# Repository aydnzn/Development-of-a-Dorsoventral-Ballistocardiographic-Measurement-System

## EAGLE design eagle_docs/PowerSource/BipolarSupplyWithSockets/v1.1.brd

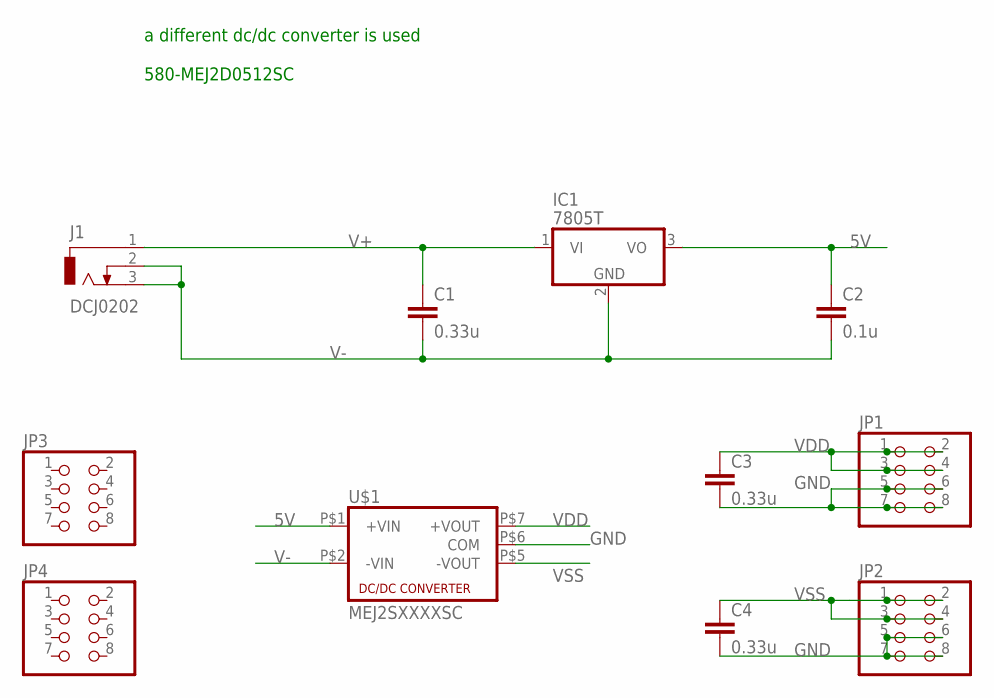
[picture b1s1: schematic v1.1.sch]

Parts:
C1, C3, C4: 0.33u; C050-045X075
C2: 0.1u; C050-045X075
IC1: 7805T; TO220H
J1: DCJ0202
JP1, JP2, JP3, JP4: PINHD-2X4; 2X04
U$1: MEJ2SXXXXSC; NMA

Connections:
5V: C2.1, IC1.3 (VO), U$1.P$1 (+VIN)
GND: C3.2, C4.2, JP1.5, JP1.6, JP1.7, JP1.8, JP2.5, JP2.6, JP2.7, JP2.8, U$1.P$6 (COM)
V+: C1.1, IC1.1 (VI), J1.1
V-: C1.2, C2.2, IC1.2 (GND), J1.2, J1.3, U$1.P$2 (-VIN)
VDD: C3.1, JP1.1, JP1.2, JP1.3, JP1.4, U$1.P$7 (+VOUT)
VSS: C4.1, JP2.1, JP2.2, JP2.3, JP2.4, U$1.P$5 (-VOUT)

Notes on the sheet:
a different dc/dc converter is used 580-MEJ2D0512SC

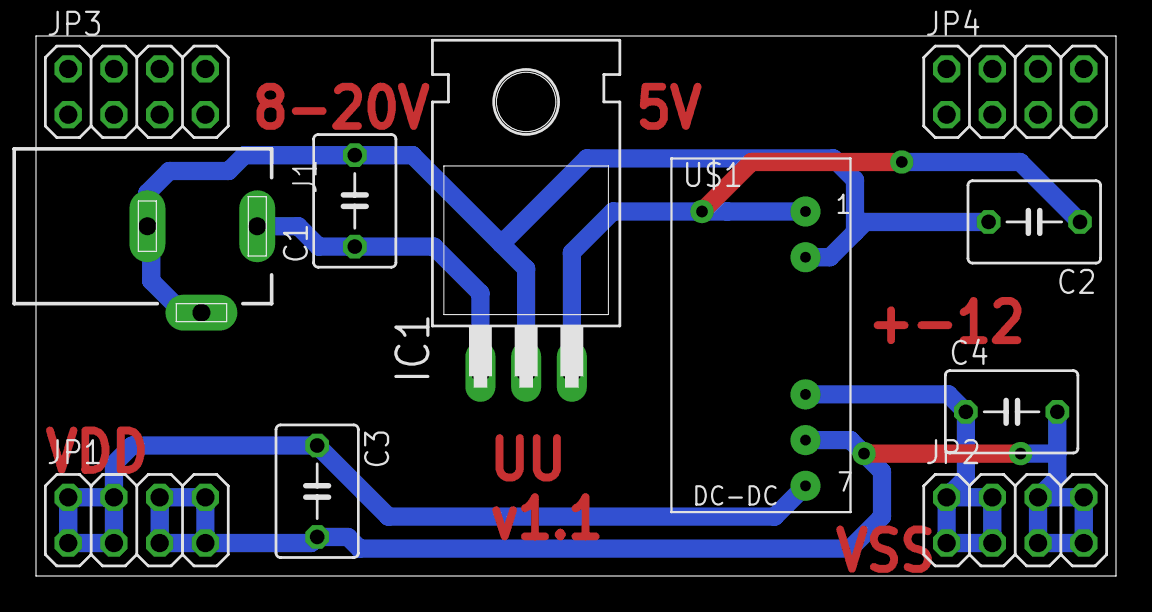
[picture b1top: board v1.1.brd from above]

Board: 2 copper layers, 60.0 x 30.0 mm, 11 parts (0 on the bottom side), 6 nets.

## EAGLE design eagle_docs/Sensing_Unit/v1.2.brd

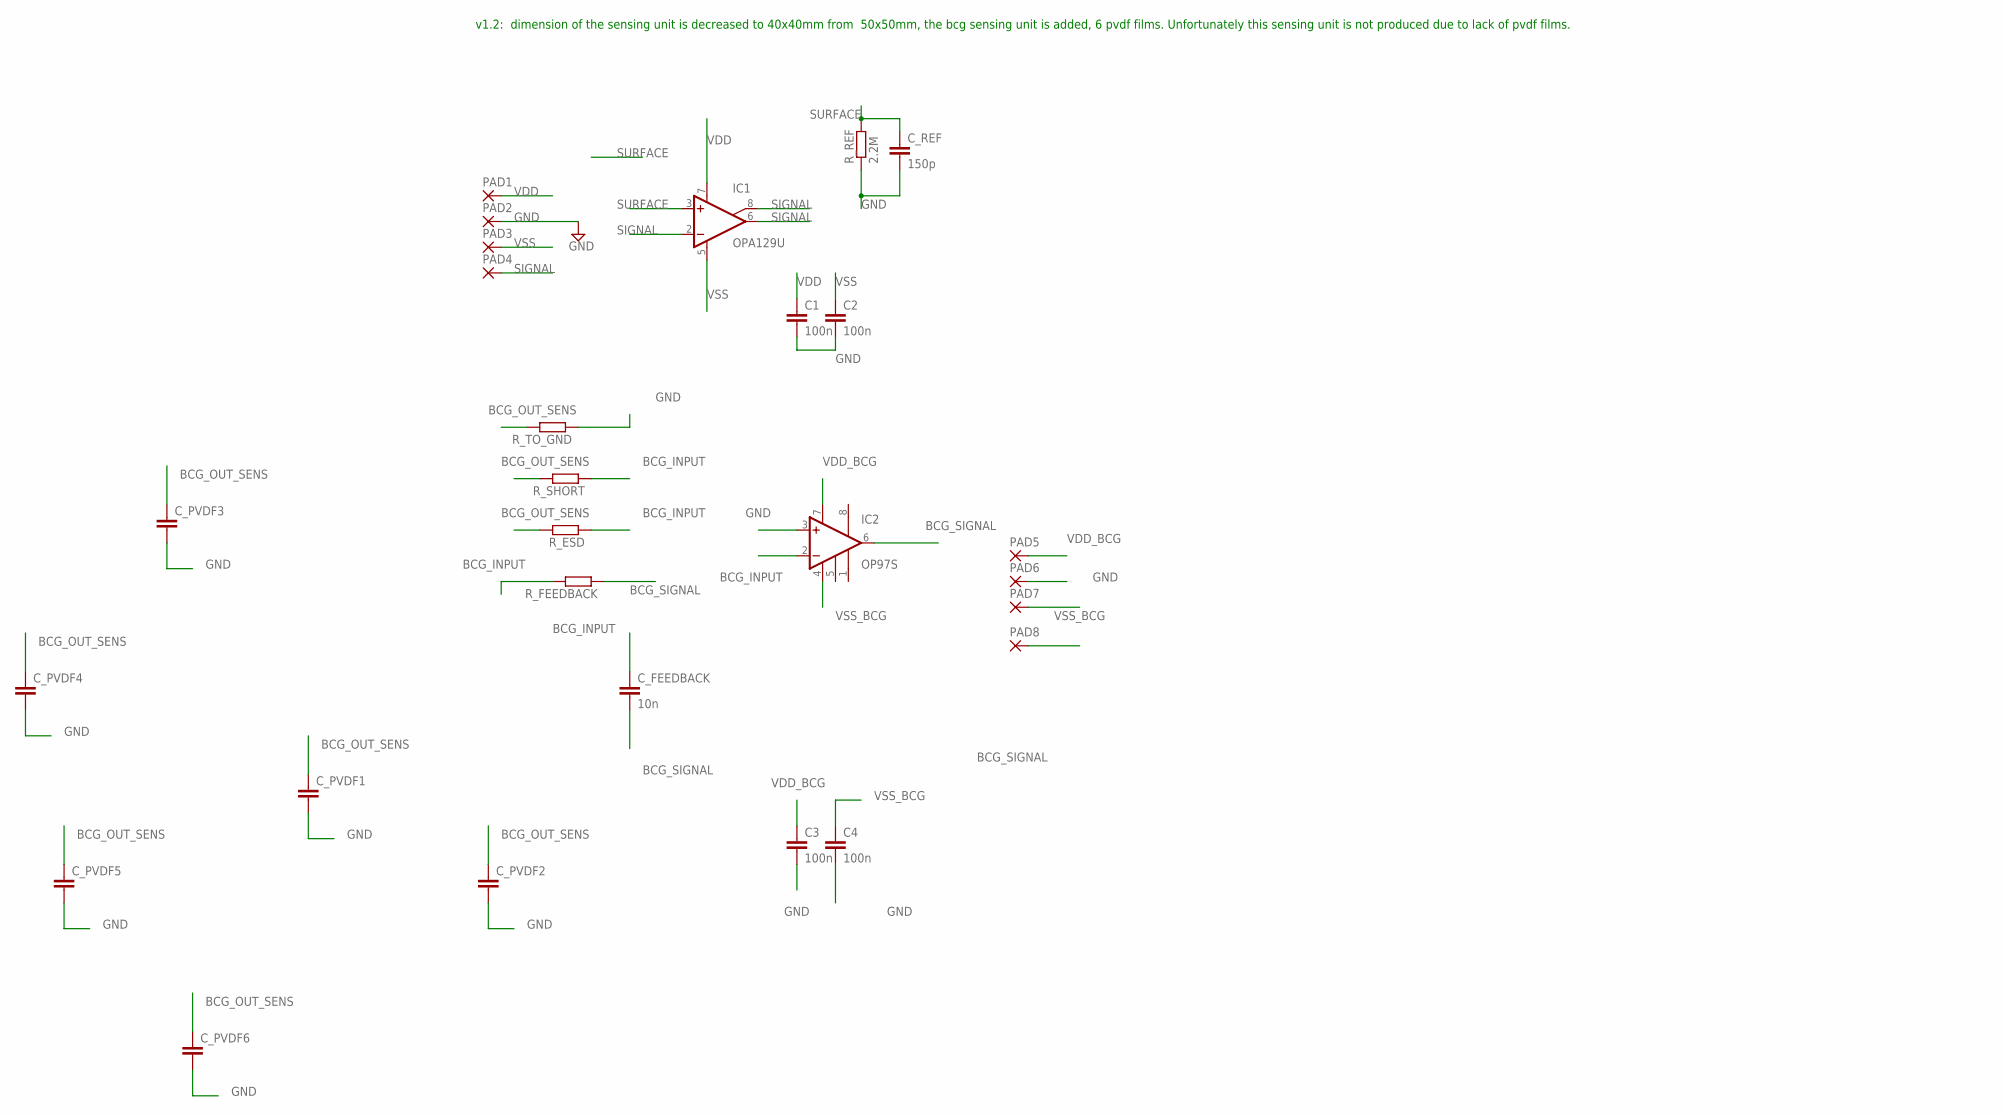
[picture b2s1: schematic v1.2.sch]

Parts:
C1, C2, C3, C4: 100n; C0805
C_FEEDBACK: 10n; C0805
C_PVDF1, C_PVDF2, C_PVDF3, C_PVDF4, C_PVDF5, C_PVDF6: C-EUC0805; C0805
C_REF: 150p; C0805
IC1: OPA129U; SO08
IC2: OP97S; SO08
PAD1, PAD2, PAD3, PAD4, PAD5, PAD6, PAD7, PAD8: SMD5; SMD2,54-5,08
R_ESD: 1M; M0805
R_FEEDBACK: 100M; M0805
R_REF: 2.2M; M0805
R_SHORT: 1M; M0805
R_TO_GND: 1M; M0805

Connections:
BCG_INPUT: C_FEEDBACK.1, IC2.2 (-IN), R_ESD.1, R_FEEDBACK.2, R_SHORT.1
BCG_OUT_SENS: C_PVDF1.1, C_PVDF2.1, C_PVDF3.1, C_PVDF4.1, C_PVDF5.1, C_PVDF6.1, R_ESD.2, R_SHORT.2, R_TO_GND.2
BCG_SIGNAL: C_FEEDBACK.2, IC2.6 (OUT), PAD8.1, R_FEEDBACK.1
GND: C1.2, C2.2, C3.2, C4.2, C_PVDF1.2, C_PVDF2.2, C_PVDF3.2, C_PVDF4.2, C_PVDF5.2, C_PVDF6.2, C_REF.2, IC2.3 (+IN), PAD2.1, PAD6.1, R_REF.1, R_TO_GND.1
SIGNAL: IC1.2 (-IN), IC1.6 (OUT), IC1.8 (SUBS), PAD4.1
SURFACE: C_REF.1, IC1.3 (+IN), R_REF.2
VDD: C1.1, IC1.7 (V+), PAD1.1
VDD_BCG: C3.1, IC2.7 (V+), PAD5.1
VSS: C2.1, IC1.5 (V-), PAD3.1
VSS_BCG: C4.1, IC2.4 (V-), PAD7.1

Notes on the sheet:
v1.2: dimension of the sensing unit is decreased to 40x40mm from 50x50mm, the bcg sensing unit is added, 6 pvdf films. Unfortunately this sensing unit is not produced due to lack of pvdf films.

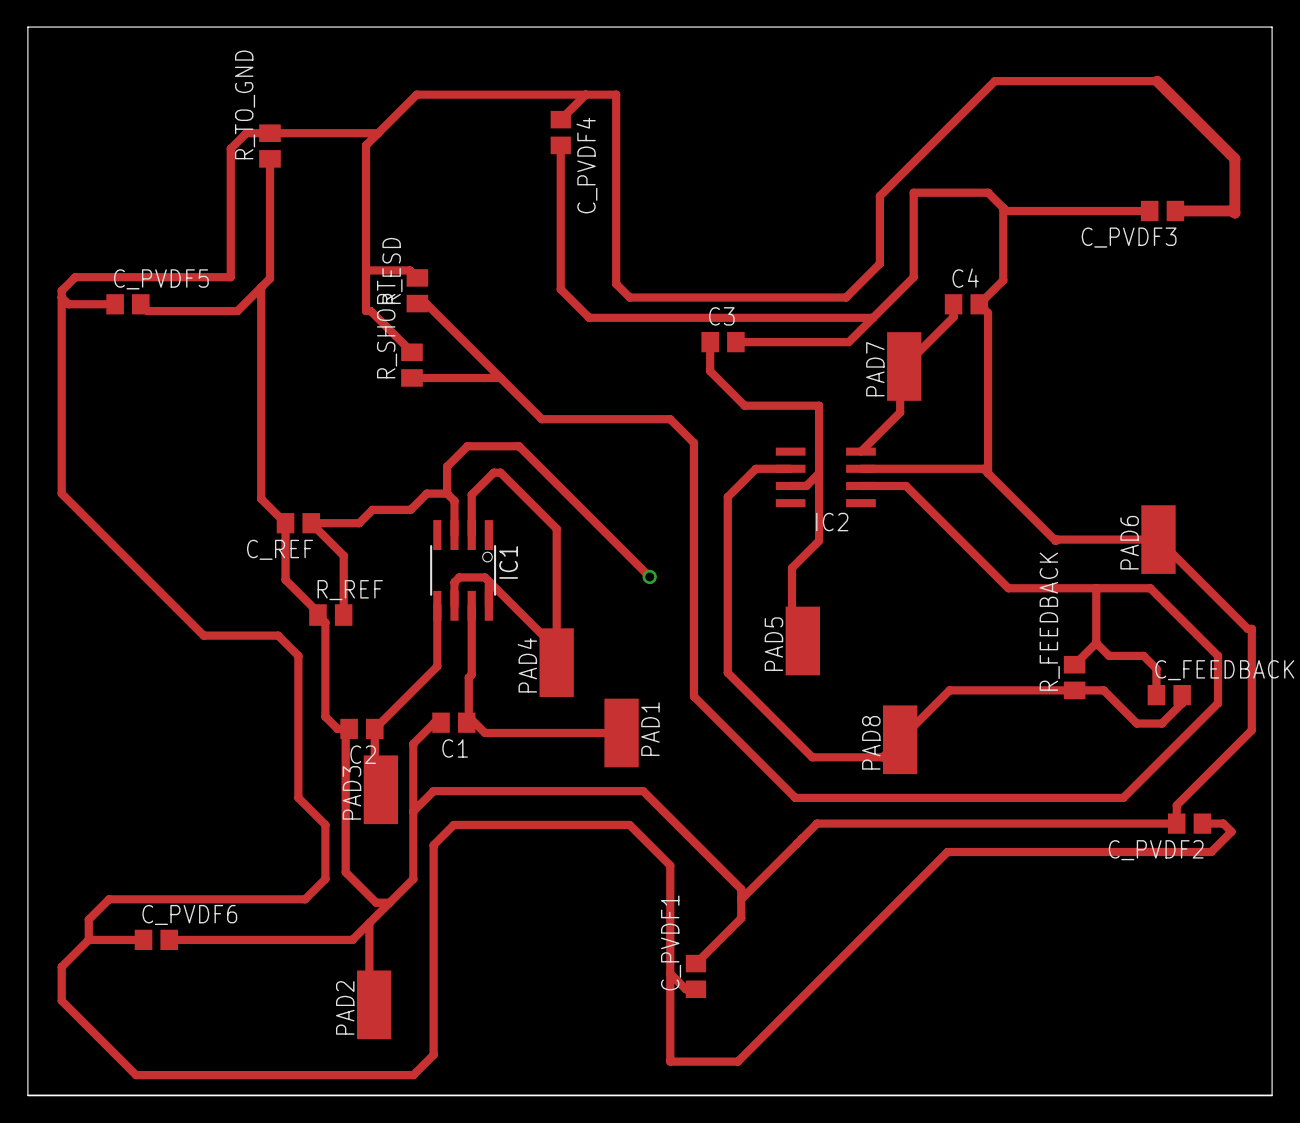
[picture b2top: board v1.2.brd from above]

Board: 2 copper layers, 92.0 x 79.0 mm, 27 parts (0 on the bottom side), 10 nets.

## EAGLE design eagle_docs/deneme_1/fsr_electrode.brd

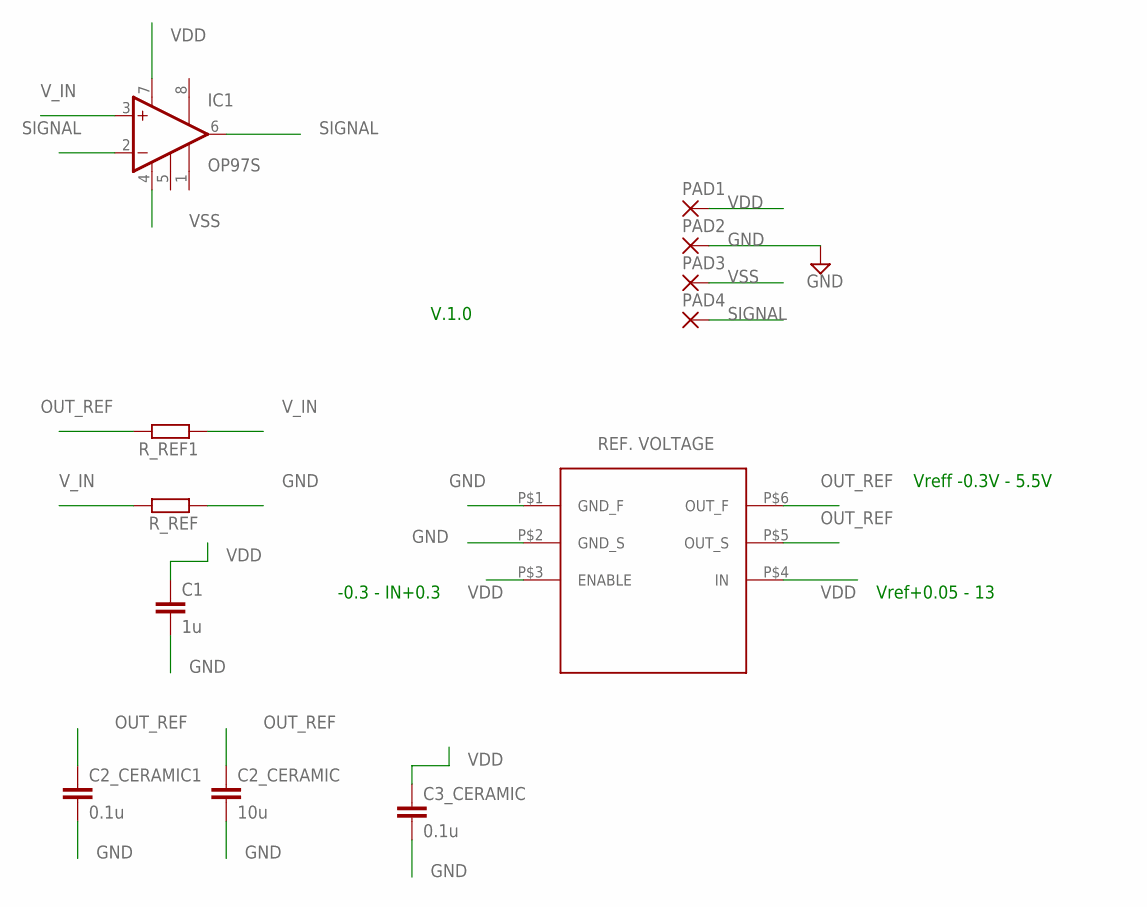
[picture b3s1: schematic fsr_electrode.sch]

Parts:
C1: 1u; C0805
C2_CERAMIC: 10u; C0805
C2_CERAMIC1, C3_CERAMIC: 0.1u; C0805
IC1: OP97S; SO08
PAD1, PAD2, PAD3, PAD4: SMD5; SMD2,54-5,08
REF3450: REF3450IDBVR; UZUN
R_REF, R_REF1: 10k; M0805

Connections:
GND: C1.2, C2_CERAMIC.2, C2_CERAMIC1.2, C3_CERAMIC.2, PAD2.1, REF3450.P$1 (GND_F), REF3450.P$2 (GND_S), R_REF.1
OUT_REF: C2_CERAMIC.1, C2_CERAMIC1.1, REF3450.P$5 (OUT_S), REF3450.P$6 (OUT_F), R_REF1.2
SIGNAL: IC1.2 (-IN), IC1.6 (OUT), PAD4.1
VDD: C1.1, C3_CERAMIC.1, IC1.7 (V+), PAD1.1, REF3450.P$3 (ENABLE), REF3450.P$4 (IN)
VSS: IC1.4 (V-), PAD3.1
V_IN: IC1.3 (+IN), R_REF.2, R_REF1.1

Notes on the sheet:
V.1.0
Vref+0.05 - 13
-0.3 - IN+0.3
Vreff -0.3V - 5.5V

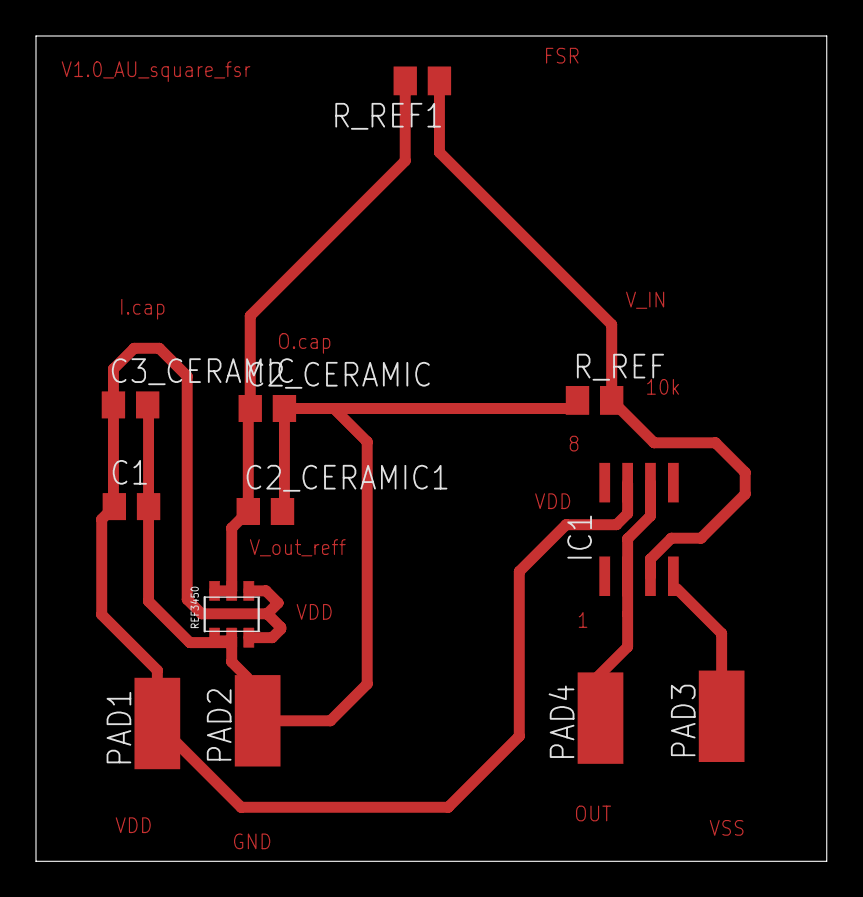
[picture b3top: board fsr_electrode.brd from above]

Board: 2 copper layers, 43.9 x 45.9 mm, 12 parts (0 on the bottom side), 6 nets.

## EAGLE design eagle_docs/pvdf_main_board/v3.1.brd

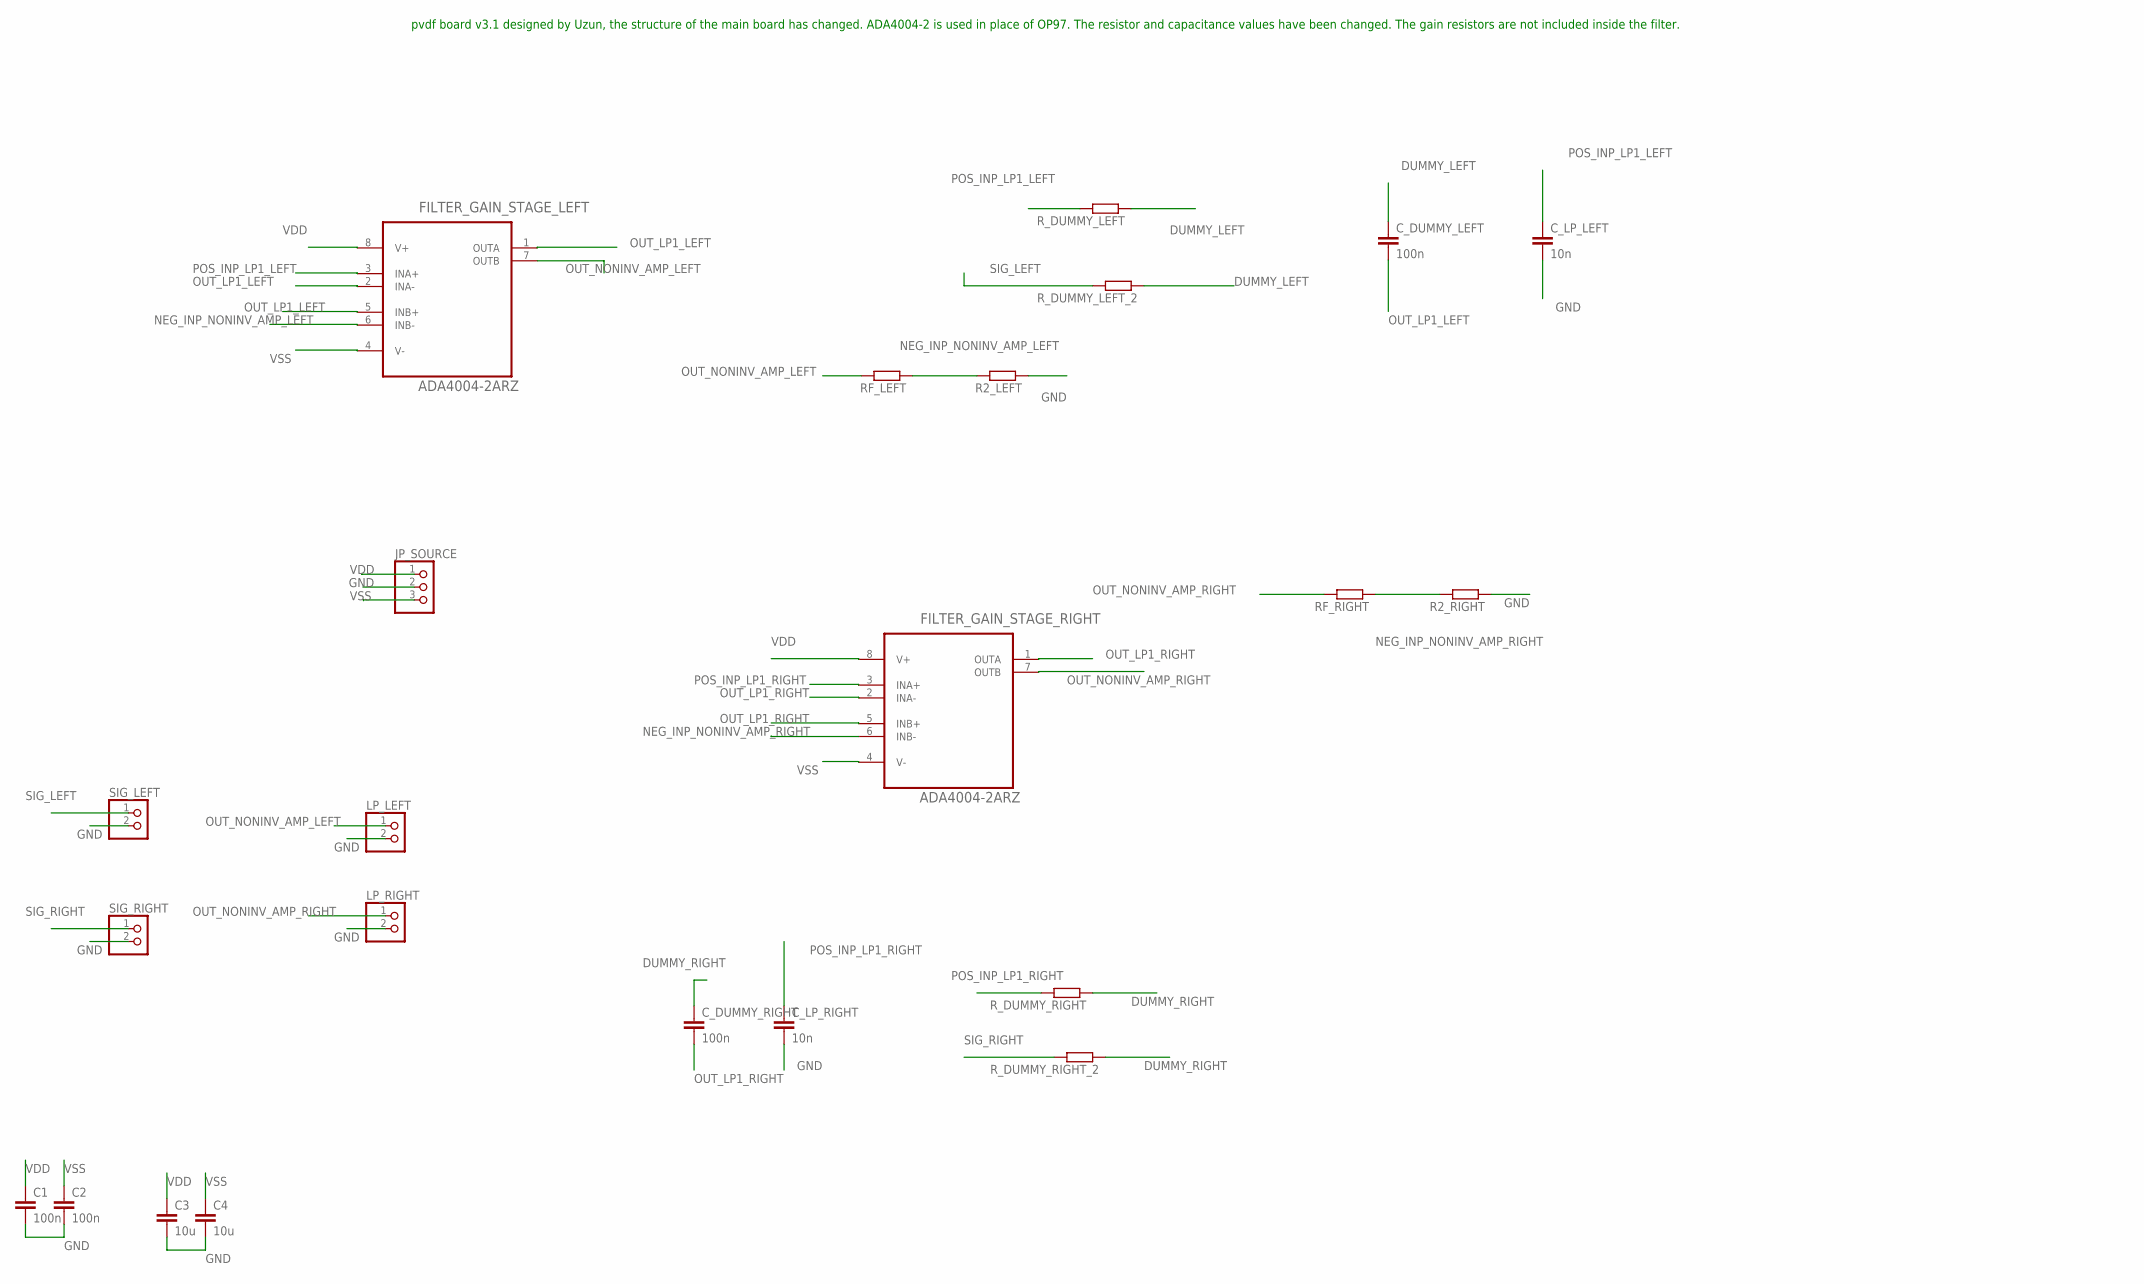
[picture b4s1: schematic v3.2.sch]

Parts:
C1, C2: 100n; C0805
C3, C4: 10u; C0805
C_DUMMY_LEFT: 100n; C0805
C_DUMMY_RIGHT: 100n; C0805
C_LP_LEFT: 10n; C0805
C_LP_RIGHT: 10n; C0805
FILTER_GAIN_STAGE_LEFT: ADA4004-2ARZ; SOIC127P600X175-8N
FILTER_GAIN_STAGE_RIGHT: ADA4004-2ARZ; SOIC127P600X175-8N
JP_SOURCE: PINHD-1X3; 1X03
LP_LEFT: PINHD-1X2; 1X02
LP_RIGHT: PINHD-1X2; 1X02
R2_LEFT, R2_RIGHT: 6.8k; M0805
RF_LEFT: 330k; M0805
RF_RIGHT: 330k; M0805
R_DUMMY_LEFT: 1M; M0805
R_DUMMY_LEFT_2: 68k; M0805
R_DUMMY_RIGHT: 1M; M0805
R_DUMMY_RIGHT_2: 68k; M0805
SIG_LEFT: PINHD-1X2; 1X02
SIG_RIGHT: PINHD-1X2; 1X02

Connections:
DUMMY_LEFT: C_DUMMY_LEFT.1, R_DUMMY_LEFT.1, R_DUMMY_LEFT_2.1
DUMMY_RIGHT: C_DUMMY_RIGHT.1, R_DUMMY_RIGHT.1, R_DUMMY_RIGHT_2.1
GND: C1.2, C2.2, C3.2, C4.2, C_LP_LEFT.2, C_LP_RIGHT.2, JP_SOURCE.2, LP_LEFT.2, LP_RIGHT.2, R2_LEFT.1, R2_RIGHT.1, SIG_LEFT.2, SIG_RIGHT.2
NEG_INP_NONINV_AMP_LEFT: FILTER_GAIN_STAGE_LEFT.6 (INB-), R2_LEFT.2, RF_LEFT.1
NEG_INP_NONINV_AMP_RIGHT: FILTER_GAIN_STAGE_RIGHT.6 (INB-), R2_RIGHT.2, RF_RIGHT.1
OUT_LP1_LEFT: C_DUMMY_LEFT.2, FILTER_GAIN_STAGE_LEFT.1 (OUTA), FILTER_GAIN_STAGE_LEFT.2 (INA-), FILTER_GAIN_STAGE_LEFT.5 (INB+)
OUT_LP1_RIGHT: C_DUMMY_RIGHT.2, FILTER_GAIN_STAGE_RIGHT.1 (OUTA), FILTER_GAIN_STAGE_RIGHT.2 (INA-), FILTER_GAIN_STAGE_RIGHT.5 (INB+)
OUT_NONINV_AMP_LEFT: FILTER_GAIN_STAGE_LEFT.7 (OUTB), LP_LEFT.1, RF_LEFT.2
OUT_NONINV_AMP_RIGHT: FILTER_GAIN_STAGE_RIGHT.7 (OUTB), LP_RIGHT.1, RF_RIGHT.2
POS_INP_LP1_LEFT: C_LP_LEFT.1, FILTER_GAIN_STAGE_LEFT.3 (INA+), R_DUMMY_LEFT.2
POS_INP_LP1_RIGHT: C_LP_RIGHT.1, FILTER_GAIN_STAGE_RIGHT.3 (INA+), R_DUMMY_RIGHT.2
SIG_LEFT: R_DUMMY_LEFT_2.2, SIG_LEFT.1
SIG_RIGHT: R_DUMMY_RIGHT_2.2, SIG_RIGHT.1
VDD: C1.1, C3.1, FILTER_GAIN_STAGE_LEFT.8 (V+), FILTER_GAIN_STAGE_RIGHT.8 (V+), JP_SOURCE.1
VSS: C2.1, C4.1, FILTER_GAIN_STAGE_LEFT.4 (V-), FILTER_GAIN_STAGE_RIGHT.4 (V-), JP_SOURCE.3

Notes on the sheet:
pvdf board v3.1 designed by Uzun, the structure of the main board has changed. ADA4004-2 is used in place of OP97. The resistor and capacitance values have been changed. The gain resistors are not included inside the filter.

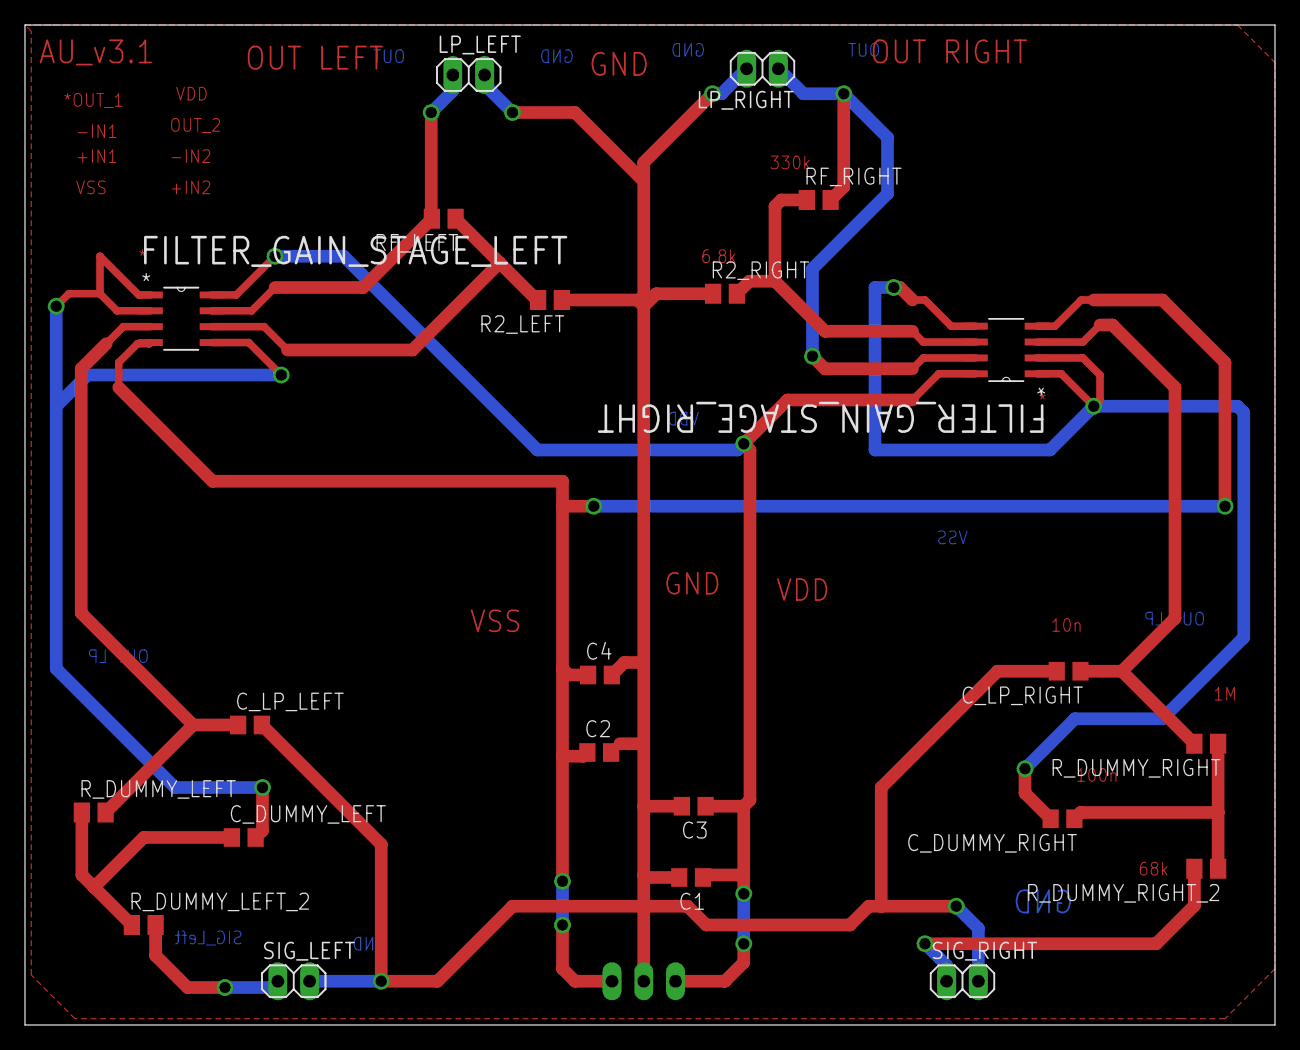
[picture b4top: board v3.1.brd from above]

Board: 2 copper layers, 100.0 x 80.0 mm, 23 parts (1 on the bottom side), 15 nets.

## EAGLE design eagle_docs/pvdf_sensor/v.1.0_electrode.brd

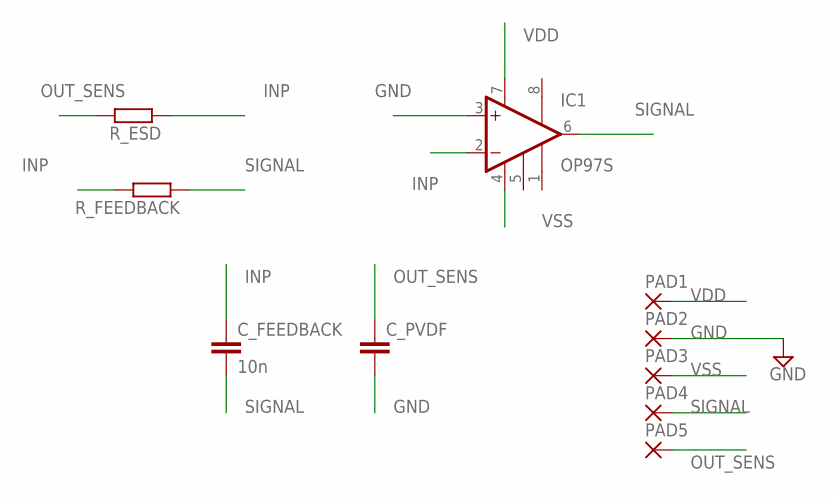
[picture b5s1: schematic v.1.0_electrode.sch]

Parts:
C_FEEDBACK: 10n; C0805
C_PVDF: C-EUC0805; C0805
IC1: OP97S; SO08
PAD1, PAD2, PAD3, PAD4, PAD5: SMD5; SMD2,54-5,08
R_ESD: 10k; M0805
R_FEEDBACK: 100M; M0805

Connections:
GND: C_PVDF.2, IC1.3 (+IN), PAD2.1
INP: C_FEEDBACK.1, IC1.2 (-IN), R_ESD.1, R_FEEDBACK.2
OUT_SENS: C_PVDF.1, PAD5.1, R_ESD.2
SIGNAL: C_FEEDBACK.2, IC1.6 (OUT), PAD4.1, R_FEEDBACK.1
VDD: IC1.7 (V+), PAD1.1
VSS: IC1.4 (V-), PAD3.1

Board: 2 copper layers, 10 parts (0 on the bottom side), 6 nets, no tracks yet.

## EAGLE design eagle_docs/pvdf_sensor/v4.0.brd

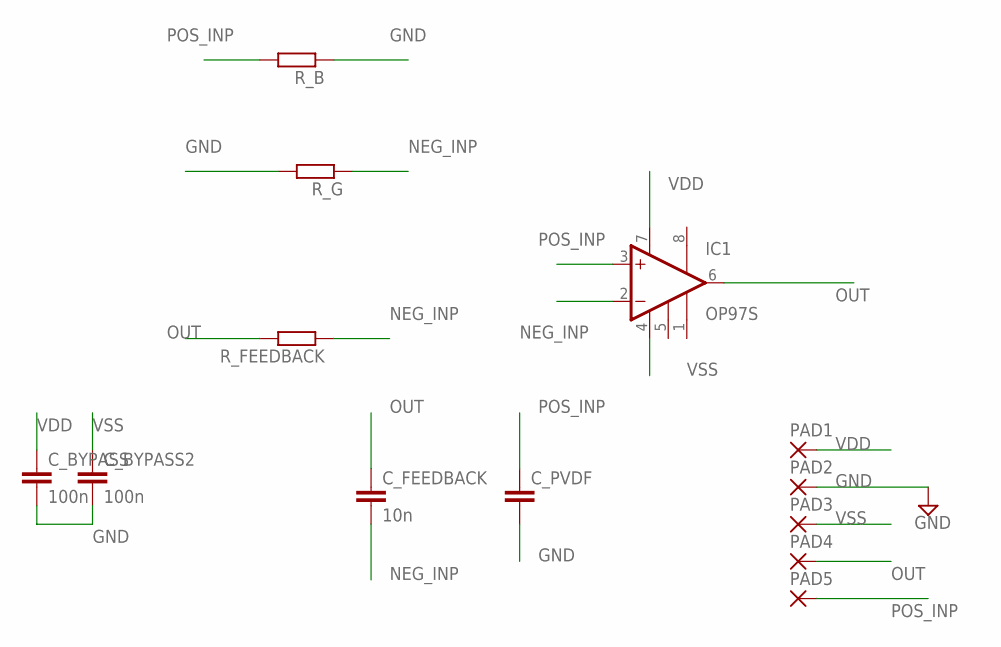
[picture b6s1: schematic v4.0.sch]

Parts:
C_BYPASS, C_BYPASS2: 100n; C0805
C_FEEDBACK: 10n; C0805
C_PVDF: C-EUC0805; C0805
IC1: OP97S; SO08
PAD1, PAD2, PAD3, PAD4, PAD5: SMD5; SMD2,54-5,08
R_B: 100M; M0805
R_FEEDBACK: 200k; M0805
R_G: 10k; M0805

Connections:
GND: C_BYPASS.2, C_BYPASS2.2, C_PVDF.2, PAD2.1, R_B.1, R_G.2
NEG_INP: C_FEEDBACK.2, IC1.2 (-IN), R_FEEDBACK.1, R_G.1
OUT: C_FEEDBACK.1, IC1.6 (OUT), PAD4.1, R_FEEDBACK.2
POS_INP: C_PVDF.1, IC1.3 (+IN), PAD5.1, R_B.2
VDD: C_BYPASS.1, IC1.7 (V+), PAD1.1
VSS: C_BYPASS2.1, IC1.4 (V-), PAD3.1

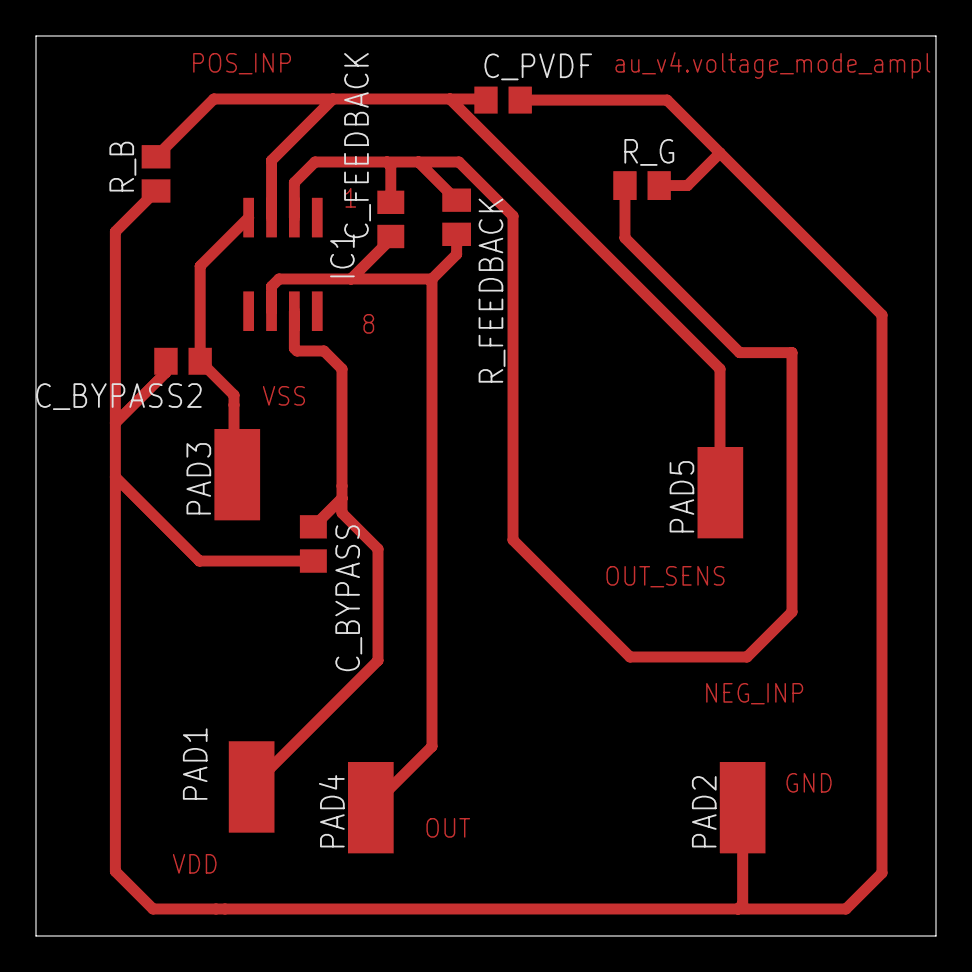
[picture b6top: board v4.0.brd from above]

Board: 2 copper layers, 50.0 x 50.0 mm, 13 parts (0 on the bottom side), 6 nets.
